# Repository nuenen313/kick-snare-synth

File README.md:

# kick-snare-synth

[Kick drum](https://youtu.be/yz37Yz315eU?si=u0BvMtUQROR8WUd3) and [snare](https://youtu.be/hULEn2_4Unw?si=4UPIrMaKqMQ0DfQr) circuits are based on [Moritz Klein's](www.youtube.com/@MoritzKlein0) yt videos.

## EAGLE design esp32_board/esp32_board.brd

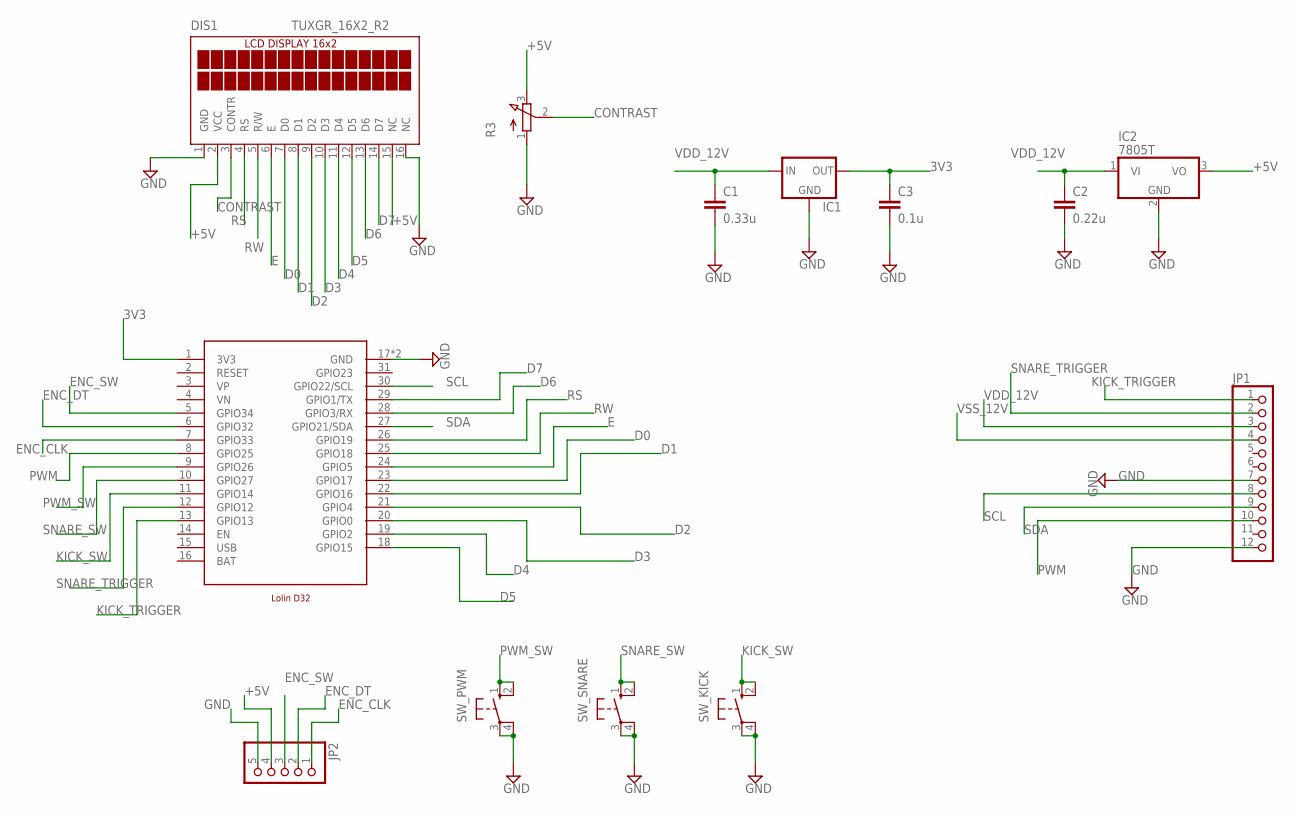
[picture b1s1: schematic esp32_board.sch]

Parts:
C1: 0.33u; C025-025X050
C2: 0.22u; C025-025X050
C3: 0.1u; C025-025X050
DIS1: TUXGR_16X2_R2
IC1: 78XXL
IC2: 7805T; TO220H
JP1: PINHD-1X12/90; 1X12/90
JP2: PINHD-1X5; 1X05
R3: 3RP/1610N
SW_KICK: 10-XX; B3F-10XX
SW_PWM: 10-XX; B3F-10XX
SW_SNARE: 10-XX; B3F-10XX
U$1: LOLIND32

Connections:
3V3: C3.1, IC1.OUT, U$1.1 (3V3)
+5V: DIS1.2 (VCC), DIS1.15 (NC), IC2.3 (VO), JP2.4, R3.3 (E)
BAT: U$1.16 (BAT)
CONTRAST: DIS1.3 (CONTR), R3.2 (S)
D0: DIS1.7 (D0), U$1.23 (GPIO17)
D1: DIS1.8 (D1), U$1.22 (GPIO16)
D2: DIS1.9 (D2), U$1.21 (GPIO4)
D3: DIS1.10 (D3), U$1.20 (GPIO0)
D4: DIS1.11 (D4), U$1.19 (GPIO2)
D5: DIS1.12 (D5), U$1.18 (GPIO15)
D6: DIS1.13 (D6), U$1.28 (GPIO3/RX)
D7: DIS1.14 (D7), U$1.29 (GPIO1/TX)
E: DIS1.6 (E), U$1.24 (GPIO5)
ENC_CLK: JP2.1, U$1.7 (GPIO33)
ENC_DT: JP2.2, U$1.6 (GPIO32)
ENC_SW: JP2.3, U$1.5 (GPIO34)
GND: C1.2, C2.2, C3.2, DIS1.1 (GND), DIS1.16 (NC), IC1.GND, IC2.2 (GND), JP1.7, JP1.12, JP2.5, R3.1 (A), SW_KICK.3, SW_KICK.4 (P1), SW_PWM.3, SW_PWM.4 (P1), SW_SNARE.3, SW_SNARE.4 (P1), U$1.17 (GND), U$1.32 (GND)
KICK_SW: SW_KICK.1 (S), SW_KICK.2 (S1), U$1.11 (GPIO14)
KICK_TRIGGER: JP1.1, U$1.13 (GPIO13)
PWM: JP1.10, U$1.8 (GPIO25)
PWM_SW: SW_PWM.1 (S), SW_PWM.2 (S1), U$1.9 (GPIO26)
RS: DIS1.4 (RS), U$1.26 (GPIO19)
RW: DIS1.5 (R/W), U$1.25 (GPIO18)
SCL: JP1.8, U$1.30 (GPIO22/SCL)
SDA: JP1.9, U$1.27 (GPIO21/SDA)
SNARE_SW: SW_SNARE.1 (S), SW_SNARE.2 (S1), U$1.10 (GPIO27)
SNARE_TRIGGER: JP1.2, U$1.12 (GPIO12)
USB: U$1.15 (USB)
VDD_12V: C1.1, C2.1, IC1.IN, IC2.1 (VI), JP1.3
VSS_12V: JP1.4

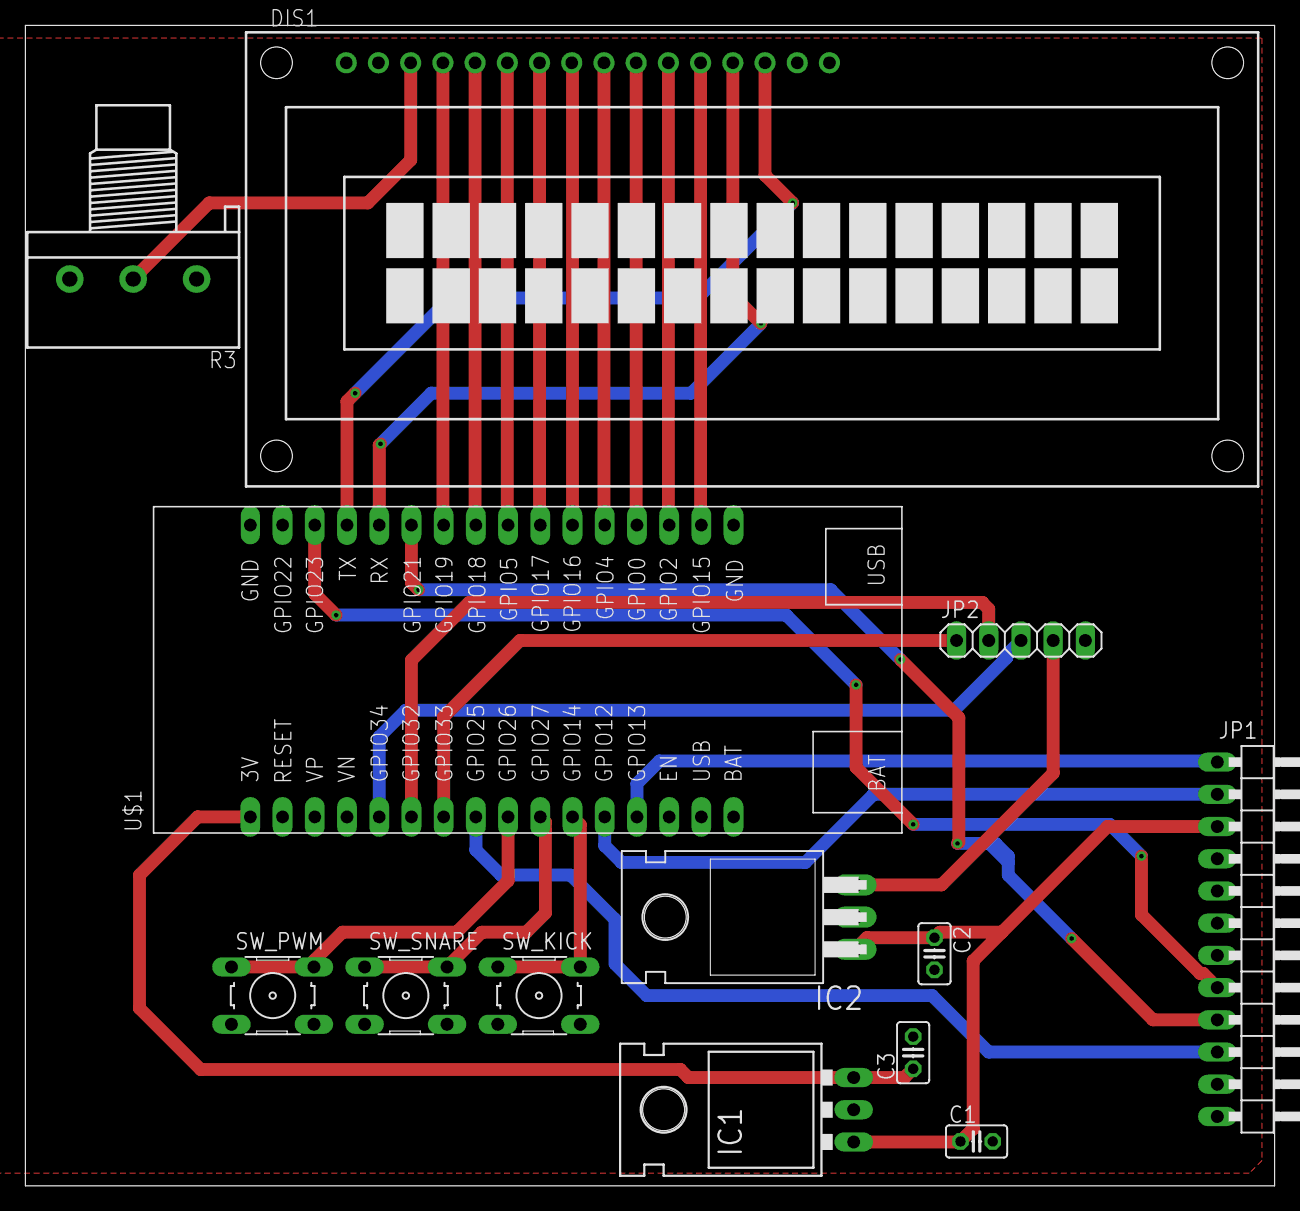
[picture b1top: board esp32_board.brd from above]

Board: 2 copper layers, 98.5 x 91.5 mm, 13 parts (0 on the bottom side), 27 nets.

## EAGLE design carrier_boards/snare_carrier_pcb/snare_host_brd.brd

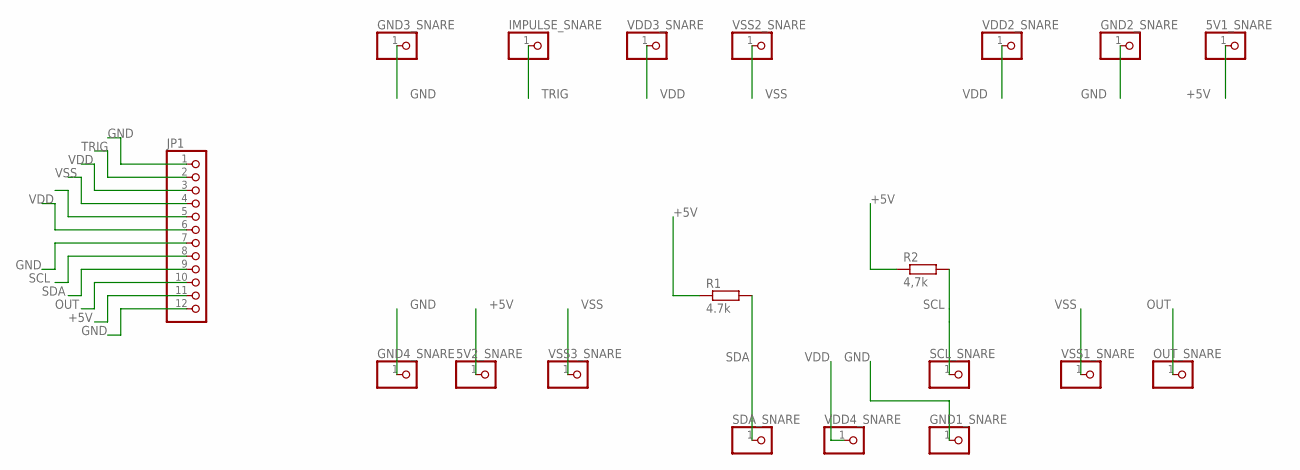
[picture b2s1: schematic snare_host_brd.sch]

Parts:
5V1_SNARE, 5V2_SNARE: PINHD-1X1; 1X01
GND1_SNARE, GND2_SNARE, GND3_SNARE, GND4_SNARE: PINHD-1X1; 1X01
IMPULSE_SNARE: PINHD-1X1; 1X01
JP1: PINHD-1X12/90; 1X12/90
OUT_SNARE: PINHD-1X1; 1X01
R1: 4.7k; 0207/10
R2: 4,7k; 0207/10
SCL_SNARE: PINHD-1X1; 1X01
SDA_SNARE: PINHD-1X1; 1X01
VDD2_SNARE, VDD3_SNARE, VDD4_SNARE: PINHD-1X1; 1X01
VSS1_SNARE, VSS2_SNARE, VSS3_SNARE: PINHD-1X1; 1X01

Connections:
+5V: 5V1_SNARE.1, 5V2_SNARE.1, JP1.11, R1.1, R2.1
GND: GND1_SNARE.1, GND2_SNARE.1, GND3_SNARE.1, GND4_SNARE.1, JP1.1, JP1.7, JP1.12
OUT: JP1.10, OUT_SNARE.1
SCL: JP1.8, R2.2, SCL_SNARE.1
SDA: JP1.9, R1.2, SDA_SNARE.1
TRIG: IMPULSE_SNARE.1, JP1.2
VDD: JP1.3, JP1.6, VDD2_SNARE.1, VDD3_SNARE.1, VDD4_SNARE.1
VSS: JP1.4, VSS1_SNARE.1, VSS2_SNARE.1, VSS3_SNARE.1

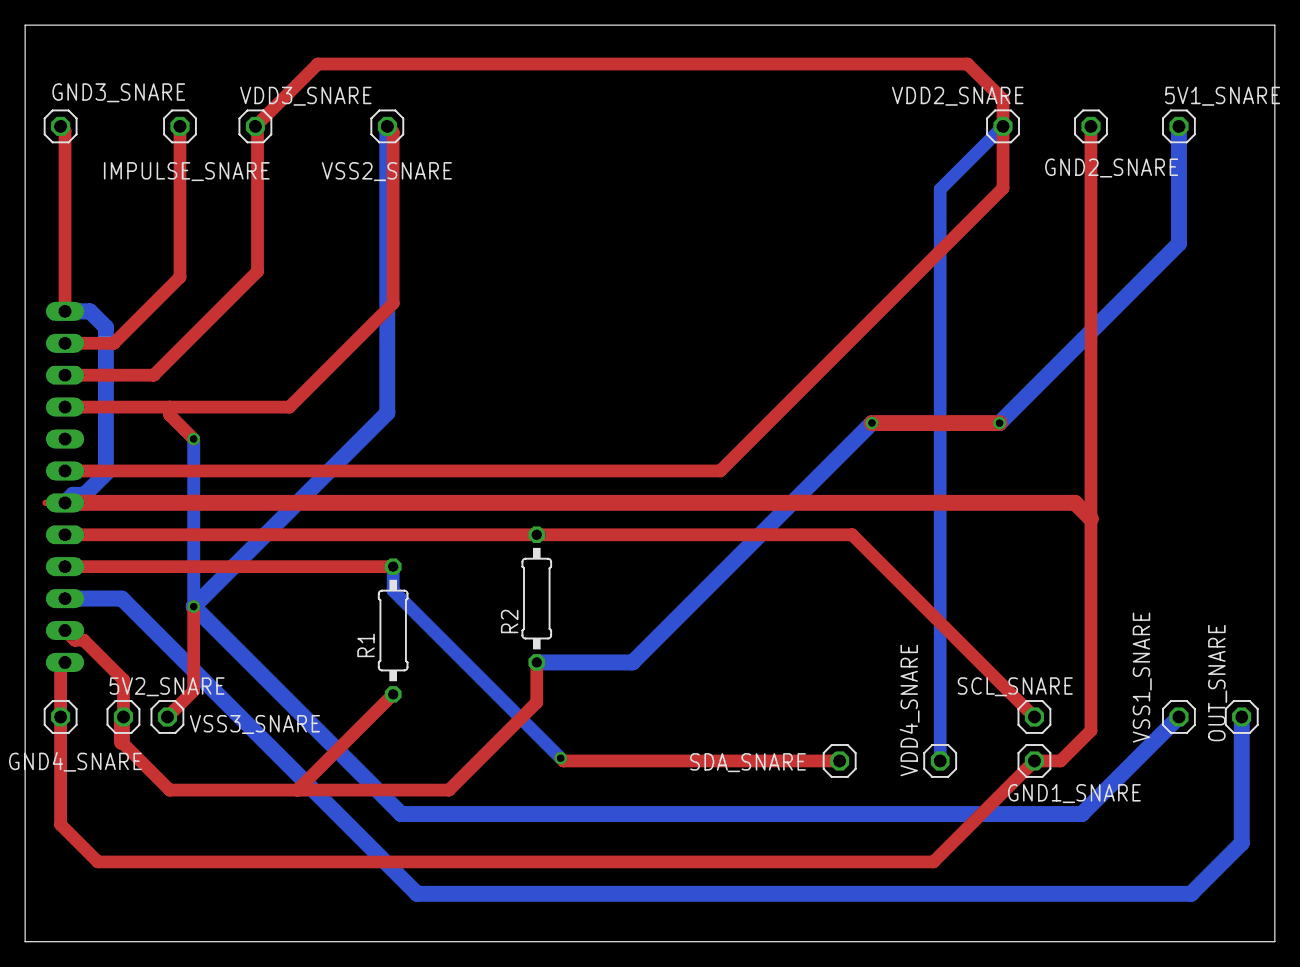
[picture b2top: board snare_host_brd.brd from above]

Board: 2 copper layers, 99.5 x 72.9 mm, 19 parts (1 on the bottom side), 8 nets.

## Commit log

2025-04-28 folders for all hardware pcbs
2025-04-28 add snare carrier board source files
2025-05-19 spice
2025-05-19 snare carrier + esp32 brd
